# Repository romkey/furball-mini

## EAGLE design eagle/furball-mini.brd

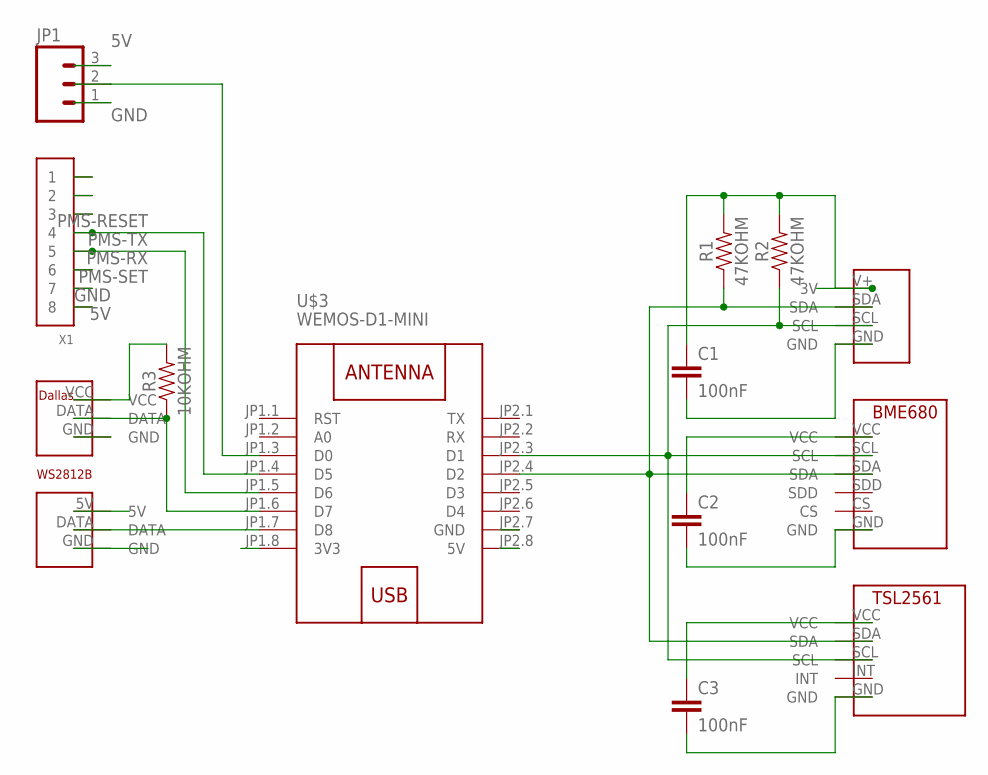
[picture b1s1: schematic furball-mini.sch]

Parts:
C1, C2, C3: 100nF; CAP-PTH-LARGE
JP1: M03PTH; 1X03
R1, R2: 47KOHM; AXIAL-0.3-KIT
R3: 10KOHM; AXIAL-0.3-KIT
U$1: WS2812BHEADER
U$2: I2CHEADER
U$3: WEMOS-D1-MINI
U$4: BME680BREAKOUT
U$5: DALLASONEWIREHEADER
U$6: TSL2561BREAKOUT
X1: CONN_8-1-53261; PB-53261-08

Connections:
3V3: C1.1, C2.1, C3.1, R1.P$2 (2), R2.P$2 (2), R3.P$2 (2), U$2.V+ (3V), U$3.JP1.8 (3V3), U$4.VCC, U$5.VCC, U$6.VCC
5V: JP1.3, U$1.5V, U$3.JP2.8 (5V), X1.8
GND: C1.2, C2.2, C3.2, JP1.1, U$1.GND, U$2.GND, U$3.JP2.7 (GND), U$4.GND, U$5.GND, U$6.GND, X1.7
unnamed: R2.P$1 (1), U$2.SCL, U$3.JP2.3 (D1), U$4.SCL, U$6.SCL
unnamed: R1.P$1 (1), U$2.SDA, U$3.JP2.4 (D2), U$4.SDA, U$6.SDA
unnamed: U$1.DATA, U$3.JP1.7 (D8)
unnamed: R3.P$1 (1), U$3.JP1.6 (D7), U$5.DATA
unnamed: JP1.2, U$3.JP1.3 (D0)
PMS-RESET: X1.3
PMS-RX: U$3.JP1.5 (D6), X1.5
PMS-SET: X1.6
PMS-TX: U$3.JP1.4 (D5), X1.4

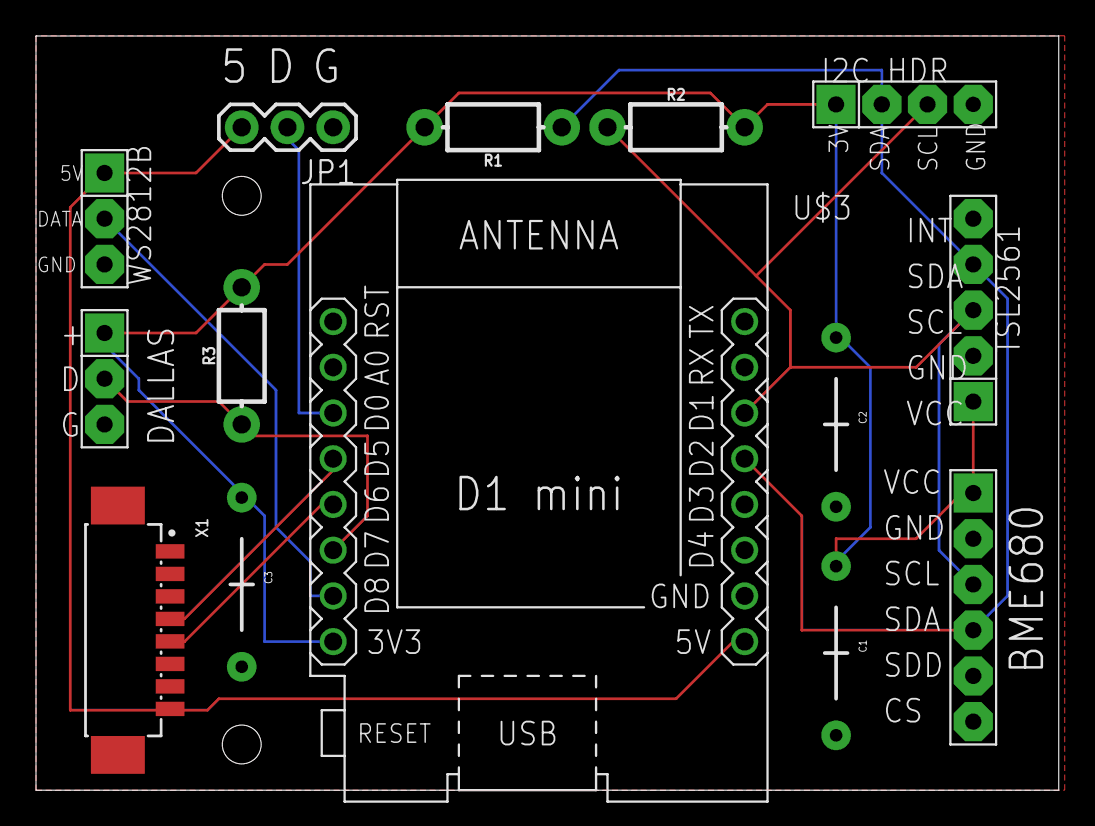
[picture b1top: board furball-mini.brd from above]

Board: 2 copper layers, 56.8 x 41.9 mm, 14 parts (0 on the bottom side), 10 nets.

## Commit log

2019-05-31 platform.ini file
2020-05-18 merged with github
2020-05-23 rewrote to work with new multiball library Homebus support, simplified and reorganized code
2020-05-23 would help to include the files with most of the logic in them
2020-05-23 added license and Eagle files
2020-07-24 sensors are now present or not present
    support new homebus message format
    get rid of LEDs
    default to BME680
2020-07-24 missing sensor header file

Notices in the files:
parts and their libraries:
diy-modules: Released under the Creative Commons Attribution 4.0 International License: http://creativecommons.org/licenses/by/4.0
